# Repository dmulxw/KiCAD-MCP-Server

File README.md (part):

# Discussions. Get in here.

https://github.com/mixelpixx/KiCAD-MCP-Server/discussions/73

> ## 🚀 Meet Konnect — the next generation
>
> **[Konnect](https://github.com/mixelpixx/Konnect)** is this project rebuilt from
> scratch in Rust as a native KiCAD 10 plugin: a single binary with no runtime
> dependencies, built on KiCAD's official IPC API instead of SWIG, with 171 tools,
> bundled Claude skills and agents, design-review audits, and a manufacturing
> pipeline. It's where new development happens — licensed AGPL-3.0 (free for
> individuals and open source; commercial licenses available for businesses).
>
> This Python/TypeScript server remains fully open (MIT) and maintained.

# KiCAD MCP Server

A Model Context Protocol (MCP) server that enables AI assistants like Claude to interact with KiCAD for PCB design automation. Built on the MCP 2025-06-18 specification, this server provides comprehensive tool schemas and real-time project state access for intelligent PCB design workflows.

## Overview

The [Model Context Protocol](https://modelcontextprotocol.io/) is an open standard from Anthropic that allows AI assistants to securely connect to external tools and data sources. This implementation provides a standardized bridge between AI assistants and KiCAD, enabling natural language control of PCB design operations.

**Key Capabilities:**

- 233 tools registered, 173 of them indexed for keyword discovery
- 173 tools across 16 categories with JSON Schema validation
- Keyword tool discovery via `search_tools` / `get_category_tools`
- 23 dynamic resources exposing project state
- Complete schematic workflow with 65 tools (authoring, batch edits, hierarchy, layout) and dynamic symbol loading (~10,000 symbols)
- Freerouting autorouter integration (Java, Docker, or Podman)
- Custom footprint and symbol creation tools
- JLCPCB parts integration with 2.5M+ component catalog and local library search
- Datasheet enrichment via LCSC
- Full MCP 2025-06-18 protocol compliance
- Cross-platform support (Linux, Windows, macOS)
- Real-time KiCAD UI integration via IPC API (experimental)
- Comprehensive error handling and logging

## Try out Arduino MCP - now you can get Claude to help in the IDE, real time!:

https://github.com/mixelpixx/arduino-ide

## What's New in v2.7.0

### The bridge no longer crosses its wires

The Node-Python protocol had no request IDs: after one timeout, the next
command was silently resolved with the _previous_ command's late result, and
every response after that was off by one. Tool calls now carry an ID that
Python echoes back; stale responses are discarded instead of mis-delivered
(#373). The MCP transport also connects before Python spawns, so clients no
longer stack up against a silent server for up to two minutes during pcbnew
warm-up (#377).

### Two file-corruption classes fixed

`add_symbol_property` dropped a closing paren on every call and could splice
a unit symbol into a top-level sibling (#362, @karu2003). And S-expression
escaping is now symmetric: reads (#336) and writes (#324) share one
escape-aware implementation, so a property value containing `\"` survives a
round-trip — 419 of KiCad's own stock symbol files carry such values.

### 8 new tools

- **Validation**: `validate_schematic`, `validate_symbol_library` — locate
  structural damage with line/column, confirmed via `kicad-cli` on a copy.
- **Library tables**: `list_library_table`, `remove_library_table_entry`,
  `set_library_table_uri` — the missing CRUD around `register_*_library`.
- **Symbol editing**: `set_symbol_pin_type` (bulk pin type fixes with
  dry-run), `find_duplicate_symbols` (the same part stored twice).
- **Back-annotation**: `backannotate_footprints` — PCB footprint choices
  flow back to the schematic, the reverse of `sync_schematic_to_board`.

All by @karu2003. With #359 (@AmirF194) registering 15 existing symbol tools,
`search_tools` now indexes 169 tools in 15 categories.

### Quality of life

- `autoroute` stages its `.dsn`/`.ses` work files in a temp directory and
  cleans up on every exit — no more litter next to your board, no stale-SES
  imports, and a killed run says "terminated externally" instead of
  `exit code 4294967295` (#249, scoped by @Dewieinns' traces).
- Placed symbols inherit the library's default Footprint (#300,
  implementation by @stefangordon).
- `add_layer` actually adds inner copper layers (#222) — it previously wrote
  to non-copper layer IDs and renamed F.SilkS.
- `sync_schematic_to_board` matches by symbol UUID, not just refdes (#250).
- JLCPCB tools decode the new upstream `source-db-v2` schema (#352,
  @stefanobaldo) and degrade gracefully when the parts DB is unavailable
  (#264, @fage2022).
- `setup-macos.sh --verify` now fails when Python requirements are missing
  instead of passing on a server that cannot start (#350, @francisrath).

Full details in the [CHANGELOG](CHANGELOG.md).

## What's New in v2.6.0

### A session-killing bug is fixed

Deleting anything from a board — a component, a trace, a board outline —
worked exactly once. The next operation, even a pure read, failed with a
`SwigPyObject` error, and only `close_project` then `open_project` recovered.
`BOARD.Remove()` hands C++ ownership to Python, so dropping the reference ran
a destructor on an object KiCad still pointed at, corrupting SWIG state
process-wide. Six call sites were affected; all now use `BOARD.Delete()`.

### 10 new tools

- **Vendor PCB import**: `import_pcb` converts PADS, Altium, Eagle, CADSTAR,
  Fabmaster, P-CAD, SolidWorks PCB and binary Cadence Allegro `.brd` files via
  KiCad 10's native importer.
- **Hierarchical schematics**: `remove_hierarchical_sheet`,
  `set_sheet_property`, `get_sheet_properties`, and `hierarchical_place` for
  arranging footprints by schematic hierarchy.
- **Schematic lint and repair**: `lint_offgrid` finds and safely snaps
  off-grid geometry that silently breaks junction placement;
  `repair_flat_symbols` fixes SnapEDA/SamacSys symbols that crash kicad-skip;
  `lint_schematic_cosmetic` tidies pin names and label orientation.
- **Board origins**: `set_board_origin` / `get_board_origin`.

### Your `.kicad_pro` net classes stop disappearing

Board saves no longer let pcbnew serialize a stale in-memory project model
over your hand-edited net classes and `netclass_patterns`. Opening a project
no longer rewrites the file at all.

### Breaking: schematic tools fail loudly on an unparseable sheet

Tools that used to return partial or empty results now return a structured
`schematic_load_failed` error naming the offending symbols. Silently skipping
a broken sheet produced an incomplete pad-to-net map reported as success,
which is worse. `repair_flat_symbols` fixes the usual cause. See
[KNOWN_ISSUES.md](docs/KNOWN_ISSUES.md) section 7.

Full details in the [CHANGELOG](CHANGELOG.md).

## What's New in v2.5.0

### 20 new board-lifecycle and geometry tools

- **Lifecycle**: `open_board`, `reload_board`, `save_board`, `save_as`,
  `is_dirty`, `discard_or_reload`, `create_board_from_schematic`.
- **Graphics editing**: `clear_board_outline`, `replace_board_outline`,
  `list_graphics`, `delete_graphic`, `update_graphic`, `move_footprint_text`.
- **Geometry queries**: `batch_move_components`, `get_component_geometry`,
  `get_pads`, `get_net_pads`, `get_ratsnest`, `estimate_airwire_lengths`,
  `check_placement_clearance`.

All of them respect backend session pinning, so a board saved while KiCad's
GUI owns the session routes to the GUI rather than writing a stale in-memory
copy — including the awkward case where `save_as` changes the board's
identity mid-session.

### Formatting is normalized and enforced

- `pre-commit run --all-files` (black, isort, prettier, flake8, mypy, eslint)
  is now a real CI gate, which is what CONTRIBUTING has always claimed.
- `npm run lint` used to run `black` in **write** mode against whatever
  `black` was on `PATH`, silently reformatting your working tree with a
  version that disagreed with CI. It now checks only; `npm run format:py` is
  the write path.
- The README's tool count is pinned to the registry by a test, so it
  self-corrects instead of drifting.

Full details in the [CHANGELOG](CHANGELOG.md).

## What's New in v2.4.1

### Three tools that were registered but had no backend now work

- `assign_net_to_class`, `check_clearance` and `set_layer_constraints` each had
  a full schema and a router entry but no dispatch handler, so every call
  returned `Unknown command`. Found by a documentation-coverage audit.
- Per-layer constraints are written to a project-scoped `.kicad_dru`
  custom-rules file, which `kicad-cli pcb drc` and the GUI both pick up — there
  is no pcbnew API for them.

### Silent failures removed

- `autoroute` was abandoned by the Node bridge at 30 s while Freerouting was
  still running, reporting failure against a valid `.ses` that existed on disk.
  Its timeout now derives from the `timeout` and `attempts` you pass.
- `get_board_2d_view` omitted `--layers` entirely when no layers were given,
  and KiCad 9+ then refuses the export — producing no file at all.
- `create_zone` raised `AttributeError` on every call over the IPC backend.

### New part-sourcing tools

- `search_parts_registry` / `get_registry_part` / `download_registry_part`
  reuse a verified existing footprint or symbol instead of generating one.
  Downloads are host-allowlisted, extension-checked and size-capped.
- `get_jlcpcb_part` returns live stock and tiered pricing when JLCPCB Open
  Platform credentials are configured, falling back to the local snapshot.

### CI now actually runs the test suite

- The Python job had been a no-op in four independent ways, and Actions was
  disabled repo-wide — 32 failed runs and 0 successes across the project's
  whole history. All 1551 Python and 63 TypeScript tests now gate every push.

Full details in the [CHANGELOG](CHANGELOG.md).

## What's New in v2.4.0

### Symbol library management

- `import_symbol` / `export_symbol` / `rename_symbol` copy a symbol between
  `.kicad_sym` libraries, extract one to a standalone file, and rename a
  symbol including its sub-symbol shards and any `(extends ...)` references
  from derived symbols in the same library.
- `add_symbol_property` and `add_library_symbol_property` set custom BOM
  fields (Manufacturer, MPN, LCSC, ...) on a library symbol or on a
  schematic's cached definition.
- `update_symbol_from_library` refreshes cached `lib_symbols` definitions
  across one schematic, a list, or every project under a directory —
  the programmatic equivalent of KiCad's Update Symbol from Library.
- `replace_instance_lib_ids` swaps `lib_id` references per an explicit
  old-to-new mapping, for migrating a schematic between libraries.

### Faster symbol discovery

- Library directories, resolved paths, extracted symbol blocks, and parsed
  symbol lists are now cached process-wide instead of being rebuilt for every
  component add. Staleness guards revalidate paths and track source `mtime_ns`,
  and the mutating write paths clear the caches explicitly.

### Fixes that restore basic operation

- Every `.kicad_sym` and schematic write raised `TypeError` on Python 3.9, the
  project's declared floor — `Path.write_text` did not accept `newline` until
  3.10.
- JLCPCB part search could not find hyphenated MPNs.
- Eagle import wrote a KiCad 9 schematic header; it now writes the KiCad 10
  header, verified against real `kicad-cli` 10.0.
- Component placement snaps to the 1.27 mm grid, `import_ses` no longer
  creates phantom slashless nets, and `export_dsn`/`autoroute` keep
  `.kicad_pro` net classes.

Full details in the [CHANGELOG](CHANGELOG.md).

## What's New in v2.3.1

### Eagle schematic import

- `import_eagle_schematic` converts Eagle `.sch` XML designs to KiCad format
  with symbol mapping, net wires, multi-gate parts, dangling-wire pruning,
  and ground-truth ERC reporting via `kicad-cli`.

### 3D model tools and interactive reload

- `add_component_3d_model` / `remove_component_3d_model` for attaching
  STEP/WRL models to footprints.
- Opt-in `KICAD_INTERACTIVE_SCHEMATIC=1` auto-confirms KiCad's reload dialog
  on Windows after schematic writes.

### Scaffolding cluster complete

- New projects start blank (no `_TEMPLATE_*` symbols leaked into user files).
- `.kicad_pro` files match what KiCad itself writes.
- Format version `20260101` ensures all KiCad 10.0.x builds can open
  generated schematics.

### KiCad 10 compatibility

- Derived symbols in `.kicad_symdir` libraries resolve their parent from
  sibling shards.
- Unified install discovery finds relocated Windows installs via registry.
- User env-var placeholders from `kicad_common.json` are resolved in library
  paths.
- Phantom cross-unit pin reports in `get_wire_connections` are eliminated.

Full details in the [CHANGELOG](CHANGELOG.md).

## What's New in v2.3.0

### Schematic corruption on KiCad 10 — both mechanisms fixed

- **Complete instance blocks**: placed components now carry the real project
  name, root-sheet uuid path, per-pin uuid entries (ERC can bind wires to
  pins), and the full KiCad 10 field set — verified byte-equivalent to what
  eeschema itself writes. Previously, dragging or editing a placed symbol
  could crash KiCad.
- **Canonical multi-line writes**: schematic tools no longer minify the whole
  file onto one line. Tool writes now match eeschema's "Save" byte-for-byte,
  with a self-check on every write that can never corrupt data. Already-
  minified files are repairable with `scripts/kicad_sch_reformat.py`.

### Your edits are protected

- **Backend session pinning**: a loaded project stays on one backend
  (SWIG or IPC) for its whole lifecycle — saves can no longer silently route
  to a stale GUI board and lose your edits.
- **External-edit guard**: `save_project` refuses to overwrite a board file
  whose contents changed on disk since load (pass `force: true` to override).
- **`close_project`** (new tool): release the project so files can be edited
  directly, then reopen — no more restart choreography.

### Works on a stock Windows install

- `kicad-cli` and 7-Zip are resolved from their install locations even when
  not on PATH — un-breaking exports, ERC/DRC, netlists, board views, and the
  JLCPCB database download, each with actionable errors when truly missing.

### New layout tools

- `suggest_placement`: connectivity-driven PCB placement optimizer (dry-run
  by default, deterministic).
- `suggest_schematic_declutter`: re-orients overlapping net labels without
  touching connectivity.

Plus KiCad 10 compatibility fixes (sheet renames, sharded `.kicad_symdir`
libraries, IPC `Box2` board size), correct pin geometry for rotated+mirrored
and multi-unit symbols, bounded IPC connects with SWIG fallback, and a real
Vitest suite for the TypeScript layer. Full details in the
[CHANGELOG](CHANGELOG.md).

## What's New in v2.2.3

### New Tools: FFC/Ribbon Cable Passthrough Workflow

A complete workflow for designing passthrough adapter boards (e.g. Raspberry Pi CSI
cable adapters) is now supported:

1. `connect_passthrough` — wires all pins of one connector to the matching pins of
   another in the schematic (J1 pin N → J2 pin N, auto-named nets).
2. `sync_schematic_to_board` — imports the net assignments into the PCB.
3. `route_pad_to_pad` — routes each connection with automatic via insertion when
   pads are on opposite copper layers.
4. `snapshot_project` — saves a named checkpoint into `<project>/snapshots/`.

### Bug Fixes (KiCAD 9 / Windows)

- **Via insertion for B.Cu footprints** — `route_pad_to_pad` now correctly detects
  when a footprint is on B.Cu and inserts the required via. (KiCAD 9 SWIG returned
  `F.Cu` for all SMD pads regardless of layer — fixed.)
- **Board outline rounded corners** — `add_board_outline` now correctly applies
  `cornerRadius` when `shape="rounded_rectangle"`.
- **B.Cu placement hang** — placing a footprint on B.Cu no longer causes a ~30s
  freeze in KiCAD 9.

### Developer Mode

Set `KICAD_MCP_DEV=1` in your Claude Desktop MCP environment to automatically save
the MCP session log into the project's `logs/` folder on every `export_gerber` and
`snapshot_project` call. Useful for debugging and for attaching to GitHub issues.

```json
"env": {
  "KICAD_MCP_DEV": "1"
}
```

> **Privacy warning:** The session log contains your full tool call history
> (including file paths and design details). **Review or delete `logs/` before
> sharing a project directory publicly.**

See [CHANGELOG](CHANGELOG.md) for the full list of changes in this release.

---

## What's New in v2.1.0

### Critical Schematic Workflow Fix + Complete Wiring System (Issue #26)

The schematic workflow was completely broken in previous versions - **this is now fixed AND dramatically enhanced!**

**What was broken:**

- `create_project` only created PCB files, no schematics
- `add_schematic_component` called non-existent API methods
- Schematics couldn't be created or edited at all
- Only 13 component types available (severe limitation)
- No working wire/connection functionality

**Complete Implementation (3 Phases):**

**Phase 1: Component Placement Foundation**

- `create_project` now creates both .kicad_pcb and .kicad_sch files
- Added pre-configured template schematics with 13 common component types
- Rewrote component placement to use proper `clone()` API

**Phase 2: Dynamic Symbol Loading (BREAKTHROUGH!)**

- **Access to ALL ~10,000 KiCad symbols** from standard libraries
- Automatic detection and dynamic loading from `.kicad_sym` library files
- Zero configuration required - just specify library and symbol name
- Seamless integration with existing MCP tools
- Full S-expression parsing and injection system

**Phase 3: Intelligent Wiring System (NEW in v2.1.0)**

- **Automatic pin location discovery** with rotation support (0°, 90°, 180°, 270°)
- **Smart wire routing** (direct, orthogonal horizontal-first, orthogonal vertical-first)
- **Power symbol support** (VCC, GND, +3V3, +5V, etc.)
- **Wire graph analysis** - geometric tracing for net connectivity
- **Net label management** (local, global, hierarchical labels)
- **Netlist generation** with accurate component/pin connections

**Technical Architecture:**
The kicad-skip library cannot create symbols or wires from scratch. We implemented a comprehensive solution:

1. **Static Templates:** 13 pre-configured symbols (R, C, L, LED, etc.) for instant use
2. **Dynamic Loading:** On-demand injection of ANY symbol from KiCad libraries:
   - Parse `.kicad_sym` library files using S-expression parser
   - Inject symbol definition into schematic's `lib_symbols` section
   - Create offscreen template instance
   - Reload schematic so kicad-skip sees new template
   - Clone template to create actual component
3. **Wire Creation:** S-expression-based wire injection (bypasses kicad-skip API limitations)
4. **Pin Discovery:** Parse symbol definitions, apply rotation transformations, calculate absolute positions
5. **Connectivity Analysis:** Geometric wire tracing to build net connection graphs

**Example - Complete Circuit Creation:**

```python
# Load power symbols dynamically
loader.load_symbol_dynamically(sch_path, "power", "VCC")

# Place components with auto-rotation
ComponentManager.add_component(sch, {
    "type": "STM32F103C8Tx",
    "library": "MCU_ST_STM32F1",
    "reference": "U1",
    "x": 100, "y": 100, "rotation": 0
})

# Connect with intelligent routing
ConnectionManager.add_connection(sch_path, "U1", "1", "R1", "2", routing="orthogonal_h")

# Connect to power nets
ConnectionManager.connect_to_net(sch_path, "U1", "VDD", "VCC")

# Analyze connectivity
connections = ConnectionManager.get_net_connections(sch, "VCC", sch_path)
# Returns: [{"component": "U1", "pin": "VDD"}, {"component": "R1", "pin": "1"}]
```

**Test Results:**

- Component placement: 100% passing
- Dynamic symbol loading: 10,000+ symbols accessible
- Wire creation: 100% passing (8/8 connections in test circuit)
- Pin discovery: Rotation-aware, sub-millimeter accuracy
- Net connectivity: 100% accurate (VCC: 2 connections, GND: 4 connections)
- Netlist generation: Working with accurate pin-level connections

See [Schematic Tools Reference](docs/SCHEMATIC_TOOLS_REFERENCE.md) for the complete schematic tool documentation, and the [Headless Authoring Guide](docs/HEADLESS_AUTHORING.md) for field-tested practice driving these tools without the KiCad GUI.

### IPC Backend (Experimental)

We are currently implementing and testing the KiCAD 9.0 IPC API for real-time UI synchronization:

- Changes made via MCP tools appear immediately in the KiCAD UI
- No manual reload required when IPC is active
- Hybrid backend: uses IPC when available, falls back to SWIG API
- IPC runtime reconnect: if MCP has fallen back to SWIG, IPC-capable board
  tools retry IPC after KiCAD launches instead of staying on SWIG for the entire
  session
- 20+ commands now support IPC including routing, component placement, and zone operations

Note: IPC features are under active development and testing. Enable IPC in KiCAD via Preferences > Plugins > Enable IPC API Server.

For OpenCode on Windows, the backend can be configured as `auto`, `ipc`, or
`swig` during setup. See [OpenCode (Windows)](#opencode-windows) for the
configuration command and backend options.

### Tool Discovery

Every tool is registered individually, so an MCP client can call any of them by
name. On top of that, most tools are indexed so an assistant can find one by
keyword instead of guessing:

- **32 essential tools** that `search_tools` surfaces first, covering the
  operations nearly every session needs
- **173 tools indexed across 16 categories** (board, component, export, drc,
  schematic, library, symbol_library, symbol_pins, schematic_hierarchy,
  schematic_layout, schematic_batch, routing, autoroute, validation,
  parts-registry, digikey)
- **3 discovery tools**:
  - `list_tool_categories` - Browse all available categories
  - `get_category_tools` - View tools in a specific category
  - `search_tools` - Find tools by keyword

The remaining 60 registered tools are not indexed yet. They work exactly the
same when called by name; they simply do not appear in `search_tools` results.

**Why this matters:** the assistant can locate the right tool for your task by
keyword rather than inventing a name. Note that discovery does _not_ reduce
context: every tool schema is still sent to the client. An earlier design hid
tools behind an `execute_tool` dispatcher to save context; it was removed
because the model then invented schemas it had never been shown. See
[ROUTER_ARCHITECTURE.md](docs/ROUTER_ARCHITECTURE.md) for that history.

**Usage is seamless:** Just ask naturally - "export gerber files" or "add mounting holes" - and Claude will find and call the appropriate tools automatically.

### NEEDS TESTING - REPORT ISSUES

### JLCPCB Parts Integration (New!)

Complete integration with JLCPCB's parts catalog, providing two complementary approaches for component selection:

**Dual-Mode Architecture:**

1. **Local Symbol Libraries** - Search JLCPCB libraries installed via KiCAD Plugin and Content Manager (contributed by [@l3wi](https://github.com/l3wi))
2. **JLCPCB API Integration** - Access the complete 2.5M+ parts catalog with real-time pricing and stock data

**Key Features:**

- Real-time pricing with quantity breaks (1+, 10+, 100+, 1000+)
- Stock availability checking
- Basic vs Extended library type identification (Basic = free assembly)
- Intelligent cost optimization with alternative part suggestions
- Package-to-footprint mapping for KiCAD compatibility
- Parametric search by category, package, manufacturer
- Local SQLite database for fast offline searching
- No API credentials required for local library search

**Why this matters:** JLCPCB offers PCB assembly services where Basic parts have no assembly fee, while Extended parts charge $3 per unique component. This integration helps you find the cheapest components with the best availability, potentially saving hundreds of dollars on assembly costs for production runs.

See [JLCPCB Usage Guide](docs/JLCPCB_USAGE_GUIDE.md) for detailed setup and usage instructions.

### Comprehensive Tool Schemas

Every tool now includes complete JSON Schema definitions with:

- Detailed parameter descriptions and constraints
- Input validation with type checking
- Required vs. optional parameter specifications
- Enumerated values for categorical inputs
- Clear documentation of what each tool does

### Resources Capability

Access project state without executing tools:

- `kicad://project/current/info` - Project metadata
- `kicad://project/current/board` - Board properties
- `kicad://project/current/components` - Component list (JSON)
- `kicad://project/current/nets` - Electrical nets
- `kicad://project/current/layers` - Layer stack configuration
- `kicad://project/current/design-rules` - Current DRC settings
- `kicad://project/current/drc-report` - Design rule violations
- `kicad://board/preview.png` - Board visualization (PNG)

### Protocol Compliance

- Updated to MCP SDK 1.21.0 (latest)
- Full JSON-RPC 2.0 support
- Proper capability negotiation
- Standards-compliant error codes

## Available Tools

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
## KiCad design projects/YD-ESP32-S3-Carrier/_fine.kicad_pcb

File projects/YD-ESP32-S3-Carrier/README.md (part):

# LANFENG-ESP32-S3 载板 (Carrier Board)

把 **YD-ESP32-S3 开发板 + ES8311 语音模块 + 1.77" SPI TFT + 3.7V 锂电池** 从一堆杜邦线变成一块插起来就能用的积木。

- 板子尺寸 **100 × 64 mm**，2 层，板厚 1.6 mm
- 四角 **4 × Ø3.2 mm 非金属化螺丝孔**（NPTH，无铜），孔心内缩 4.5 mm
- 板高 64 mm 是**按开发板 USB 边缘定的**：开发板本体到 y 63.25 为止，Type-C 口整个悬在板外，装壳不挡
- 连接器：**排母为主 + 排针引出**
  - 开发板 2 × 1×22 排母（J1/J2）
  - 语音模块 1×10 排母（J3）
  - 显示屏 1×7 排针（J4）、电池 1×2 排针（J5）
  - 备用 IO 1×8 ×2（J6/J7）、串口 1×3（J9）
- 语音模块**平放**在板上（J3 上方整块区域无元件、无过孔）
- 四个按键**同在一条底边**：音量+、音量−、激活、Reset
- **板载 3.7V 锂电充电 + 升压**，USB 与电池可同时插，自动由 USB 供电

---

## 一、接线表

### 1. 开发板插到 J1 / J2（**照丝印插，别照原理图**）

两列排母间距 **25.40 mm**，脚距 2.54 mm，每列**最上方都是第 1 脚**。

> ⚠️ **重要**：开发板原理图 `J2` 的引脚编号与实物丝印**差一位**（原理图 pin1 = TXD0，实物最上方是 GND）。本载板**以实物丝印为准**，丝印上每一脚都印了 GPIO 号，插之前对一下即可。

**J1（左列，上→下）**

| 脚 | 丝印 | 脚 | 丝印 | 脚 | 丝印 |
|---|---|---|---|---|---|
| 1 | 3V3 | 9 | IO16 | 17 | IO11 |
| 2 | 3V3 | 10 | IO17 | 18 | IO12 |
| 3 | RST | 11 | IO18 | 19 | IO13 |
| 4 | IO4 | 12 | IO8 | 20 | IO14 |
| 5 | IO5 | 13 | IO3 | 21 | **5V** |
| 6 | IO6 | 14 | IO46 | 22 | GND |
| 7 | IO7 | 15 | IO9 | | |
| 8 | IO15 | 16 | IO10 | | |

**J2（右列，上→下）**

| 脚 | 丝印 | 脚 | 丝印 | 脚 | 丝印 |
|---|---|---|---|---|---|
| 1 | GND | 9 | IO39 | 17 | IO47 |
| 2 | IO43 | 10 | IO38 | 18 | IO21 |
| 3 | IO44 | 11 | IO37 | 19 | IO20 |
| 4 | IO1 | 12 | IO36 | 20 | IO19 |
| 5 | IO2 | 13 | IO35 | 21 | GND |
| 6 | IO42 | 14 | IO0 | 22 | GND |
| 7 | IO41 | 15 | IO45 | | |
| 8 | IO40 | 16 | IO48 | | |

> **J1-21 是整块板的 5V 入口**：开发板的 Type-C 收进来的 5V 从这里回灌到载板的 `+5V` 轨，
> 给功放、指示灯和充电电路供电。所以**充电宝要插在开发板的 Type-C 口**，不是载板。

### 2. 语音模块插到 J3（1×10 排母，模块**平放**）

丝印按**模块自己的引脚名**印，照着插就行：

| J3 | 1 | 2 | 3 | 4 | 5 | 6 | 7 | 8 | 9 | 10 |
|---|---|---|---|---|---|---|---|---|---|---|
| 丝印 | SDA | SCL | MCK | BCK | DI | WS | DO | 3V3 | VCC | GND |
| 接到 | GPIO1 | GPIO2 | GPIO3 | GPIO15 | GPIO7 | GPIO16 | GPIO6 | 3V3 | **5V** | GND |

> 注意 **VCC 接 5V**（模块功放取 5V），**3V3 接 3V3**，两个别接反。

### 3. 显示屏用排线引到 J4（1×7 排针）

| J4 | 1 | 2 | 3 | 4 | 5 | 6 | 7 |
|---|---|---|---|---|---|---|---|
| 丝印 | CS | DC | RST | SDA | SCK | VCC | GND |
| 接到 | GPIO41 | GPIO40 | GPIO45 | GPIO47 | GPIO21 | 3V3 | GND |

### 4. 电池接到 J5（1×2 排针，2.54 mm）

| J5 | 1 | 2 |
|---|---|---|
| 丝印 | **BAT** | GND |

接 **3.7V 聚合物锂电池**（2.54 mm 插头，红=BAT、黑=GND）。
**BAT 这一脚是电池的裸正极**，在 SW5 之前——关掉 SW5 就彻底断开电池放电，但**充电不受影响**（TP4056 直接挂在电池上）。

> v1 这一脚印的是 `+5V`，因为电池当时是直接并在 5V 轨上的。v2 中间加了升压，所以标签必须改。

### 5. 备用 IO（J6 / J7）与串口（J9）

每个 GPIO **只引一次**，两个排针没有重复脚位。

**J6 —— J1 侧空余脚**

| 脚 | 1 | 2 | 3 | 4 | 5 | 6 | 7 | 8 |
|---|---|---|---|---|---|---|---|---|
| 丝印 | 3V3 | GND | IO9 | IO10 | IO11 | IO12 | IO13 | IO14 |

**J7 —— J2 侧空余脚**

| 脚 | 1 | 2 | 3 | 4 | 5 | 6 | 7 | 8 |
|---|---|---|---|---|---|---|---|---|
| 丝印 | 3V3 | GND | IO42 | IO39 | IO38 | IO48 | IO43 | IO44 |

**J9 —— UART1**（右下角，按键上方）

| 脚 | 1 | 2 | 3 |
|---|---|---|---|
| 丝印 | IO17 | IO18 | GND |

IO17/IO18 正是 ESP32-S3 **UART1** 的 TX/RX，单独引一组当调试串口。

> **刻意不引出**：IO0 / IO46（strapping 脚）、IO19 / IO20（USB D±）、IO35 / 36 / 37（PSRAM 占用）。
> 这 7 个脚在 J1/J2 上保留焊盘但**不接任何网络**，也不引到 J6/J7。

### 6. 按键（都在底边一排）

| 按键 | 丝印 | 接到 |
|---|---|---|
| SW1 | VOL+ | GPIO4 |
| SW2 | VOL− | GPIO5 |
| SW3 | ACT | GPIO8 |
| SW4 | RESET | CHIP_PU（开发板 RST） |
| SW5 | PWR SW | 电池 → 升压（电源开关，不是按键） |

四个按键另一端全接 GND，靠 ESP32-S3 **内部上拉**，不需要外部电阻。
GPIO4 / GPIO5 / GPIO8 都避开了 strapping 脚和 USB 脚。

---

## 二、元件清单

共 **36 个封装**。

### 连接器 / 机电件

| 位号 | 值 | 封装 |
|---|---|---|
| J1, J2 | YD-ESP32-S3_L / _R | `PinSocket_1x22_P2.54mm_Vertical` |
| J3 | ES8311_AUDIO | `PinSocket_1x10_P2.54mm_Vertical` |
| J4 | TFT_1.77 | `PinHeader_1x07_P2.54mm_Vertical` |
| J5 | BAT_3V7 | `PinHeader_1x02_P2.54mm_Vertical` |
| J6, J7 | SPARE_IO_A / _B | `PinHeader_1x08_P2.54mm_Vertical` |
| J9 | UART1 | `PinHeader_1x03_P2.54mm_Vertical` |
| SW1–SW4 | VOL_UP / VOL_DN / ACTIVATE / RESET | `SW_PUSH_6mm` |
| SW5 | POWER_ON_OFF | `SW_Slide_SPDT_Straight_CK_OS102011MS2Q` |
| H1–H4 | MountingHole_3.2mm_M3 | Ø3.2 mm NPTH |

### 直插（滤波 / 指示）

| 位号 | 值 | 封装 |
|---|---|---|
| C1 | 100 µF 电解（5V 储能） | `CP_Radial_D5.0mm_P2.50mm` |
| C2 | 100 nF 瓷片（5V 去耦） | `C_Disc_D5.0mm_W2.5mm_P5.00mm` |
| C3 | 10 µF 电解（3V3） | `CP_Radial_D5.0mm_P2.50mm` |
| C4 | 100 nF（3V3 去耦） | `C_Disc_D5.0mm_W2.5mm_P5.00mm` |
| D1 | PWR_LED（电源指示） | `LED_D5.0mm` |
| R1 | 1 kΩ（D1 限流） | `R_Axial_DIN0207_L6.3mm_D2.5mm_P7.62mm_Horizontal` |

### 贴片（充电 + 升压）

| 位号 | 值 | 封装 | 作用 |
|---|---|---|---|
| U1 | TP4056 | `Package_SO:SOIC-8-1EP_3.9x4.9mm_P1.27mm_EP2.41x3.3mm_ThermalVias` | 锂电池充电 |
| U2 | MT3608 | `Package_TO_SOT_SMD:SOT-23-6` | 3.7V→4.89V 升压 |
| D2 | SS34 | `Diode_SMD:D_SMA` | 升压输出 OR 二极管 |
| D3 | CHG（充电指示） | `LED_SMD:LED_0805_2012Metric` | 充电中点亮 |
| L1 | 22 µH 屏蔽电感 | `Inductor_SMD:L_Taiyo-Yuden_NR-60xx` | 升压储能 |
| R2 | 2.4 kΩ | `Resistor_SMD:R_0805_2012Metric` | 充电电流 ≈ 500 mA |
| R3 | 1 kΩ | `Resistor_SMD:R_0805_2012Metric` | D3 限流 |
| R4 | 71.5 kΩ | `Resistor_SMD:R_0805_2012Metric` | FB 上分压 |
| R5 | 10 kΩ | `Resistor_SMD:R_0805_2012Metric` | FB 下分压 |
| C5, C6 | 10 µF | `Capacitor_SMD:C_1206_3216Metric` | TP4056 输入 / 电池侧 |
| C7, C8 | 22 µF | `Capacitor_SMD:C_1206_3216Metric` | 升压输入 / 输出 |

---

## 三、打样说明（嘉立创）

**直接上传 `gerbers/` 整个目录**即可，EDA 软件会自动识别。

| 项目 | 取值 |
|---|---|
| 尺寸 | **100 × 64 mm**（在 100×100 以内，标准价） |
| 层数 | 2 层 |
| 板厚 | 1.6 mm |
| 阻焊 / 丝印 | 默认即可 |
| 表面处理 | 有铅喷锡 / 无铅喷锡均可 |
| 最小线宽 / 间距 | 0.30 mm / 0.16 mm |
| 最小孔径 | **0.30 mm**（过孔）／**3.20 mm**（螺丝孔） |
| 过孔 | Ø0.60 / 钻孔 Ø0.30 |
| 丝印 | 最小字符高 0.80 mm、线宽 0.15 mm（满足嘉立创工艺下限） |

> **本板有 13 个贴片元件**，不是纯插件板——需要贴片焊接（见第四节）。
> 钢网层（`F_Paste` / `B_Paste`）**必须一起上传**，否则贴片无法生产。

Gerber 文件说明（Protel 扩展名，嘉立创可直接识别）：

```
gerbers/
  YD-ESP32-S3-Carrier-F_Cu.gtl          顶层铜
  YD-ESP32-S3-Carrier-B_Cu.gbl          底层铜
  YD-ESP32-S3-Carrier-F_Silkscreen.gto  顶层丝印
  YD-ESP32-S3-Carrier-B_Silkscreen.gbo  底层丝印
  YD-ESP32-S3-Carrier-F_Mask.gts        顶层阻焊
  YD-ESP32-S3-Carrier-B_Mask.gbs        底层阻焊
  YD-ESP32-S3-Carrier-F_Paste.gtp       顶层钢网（贴片用，务必上传）
  YD-ESP32-S3-Carrier-B_Paste.gbp       底层钢网
  YD-ESP32-S3-Carrier-Edge_Cuts.gm1     板框
  YD-ESP32-S3-Carrier-PTH.drl           金属化孔（插件脚 + 过孔）
  YD-ESP32-S3-Carrier-NPTH.drl          非金属化孔（4 个 Ø3.2 螺丝孔）
  YD-ESP32-S3-Carrier-*-drl_map.gbr     钻孔图（仅参考）
  YD-ESP32-S3-Carrier-job.gbrjob        Gerber 作业文件
```

---

## 四、装配注意事项

1. **先贴片，后直插**：
   `U1 U2 D2 D3 L1 R2 R3 R4 R5 C5 C6 C7 C8`（回流焊或热风）→ 按键 SW1–SW4 → 电容 C1–C4、D1、R1 → 排针 J4/J5/J6/J7/J9 → 排母 J1/J2/J3 → 最后 SW5。
2. **U1（TP4056）是 ESOP-8 带散热焊盘**，散热脚下的 9 个过孔是散热路径，纯烙铁很难焊透。**用热风枪或加热台**；只有烙铁的话，建议改买 **SOP-8 无散热焊盘版**的 TP4056 并手工替换封装。
3. **排母焊在正面**（F.Cu 那面），开发板和语音模块从正面插下去。
4. **语音模块方向**：模块主体朝板内平铺，1 脚对准 J3 丝印的 `SDA`。J3 上方整块区域（x 43–74, y 15–32）刻意留空，模块能完全放平。
5. **D1 / D3 极性**：LED 封装 1 脚是阴极（有横杠/缺口的一侧）。D1 阴极接 GND，D3 阴极接 U1 的 `CHRG`。
6. **D2（SS34）方向**：1 脚是阴极，接 `+5V` 轨；2 脚是阳极，接升压输出。**装反 = 电池供不了电**。
7. **C1 / C3 是电解电容，注意极性**：丝印上有 `+` 号的那一脚接正。
8. **螺丝孔是 Ø3.2 mm 非金属化通孔**，孔周围 2.70 mm 内没有覆铜——如果螺丝头/垫片需要落在铜面上，请在此处垫绝缘片。

---

## 五、电源设计（v2 的核心改动）

### 5.1 为什么必须升压

v1 把电池直接并在 `+5V` 轨上。那是错的，而且没法靠加二极管救：
**3.7V − 0.45V = 3.25V**，开发板的 AMS1117 压差要 1.1V，3.25V 根本推不动 3.3V 轨。

所以 v2 在电池和 5V 轨之间加了 **MT3608 升压**，并在 5V 轨上加了 **TP4056 充电**：

```
充电宝 5V ──Type-C──> 开发板 5V ──J1-21──┬──> +5V 轨 ──> J3-9(功放VCC) / C1,C2 / R1,D1 / C8 / R3,D3
                                          │
                                 D2(SS34) ┘   ← 阴极朝 +5V，阳极朝升压输出
                                     ▲
  LiPo 3.7V ──J5─┬─> U1 TP4056 (BAT) ──> 充电，直接挂在电池上
                 │
                 └─> SW5 ─> U2 MT3608 ──> D2 阳极
                              └─ FB 分压从 +5V（D2 之后）取
```

### 5.2 为什么 FB 分压取在二极管**之后**，输出定到 **4.89 V**

这是让"USB 优先"**自动**成立的关键，两个细节缺一不可：

1. **FB 取在 D2 之后（即取 `+5V`）** —— 二极管压降被反馈环包进去了，输出电压与负载电流无关。
   如果 FB 取在 D2 之前，带载时二极管压降会让 `+5V` 掉到 4.5V 以下。
2. **输出定在 4.89 V < USB 的 5.0 V** —— USB 一插上，D2 阴极 (5.0V) 高于阳极 (4.89V)，
   **二极管自然反偏截止**，升压 IC 因输出被顶高而停止开关，进入待机。
   不需要任何"检测电路"，也不需要手动切换。

分压电阻：`Vout = 0.6 × (1 + R4/R5)` → **R4 = 71.5 kΩ / R5 = 10 kΩ → 4.89 V**。

电池单独供电时 `+5V` = 4.89V，对 AMS1117（需 ≥4.4V）和功放（功率 ∝ V²，仅降 4%）都完全够用。

### 5.3 几个容易被忽略的点

- **SW5 放在电池与升压之间**，不是放在 5V 轨上。关掉即彻底切断电池放电；充电不受影响。
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
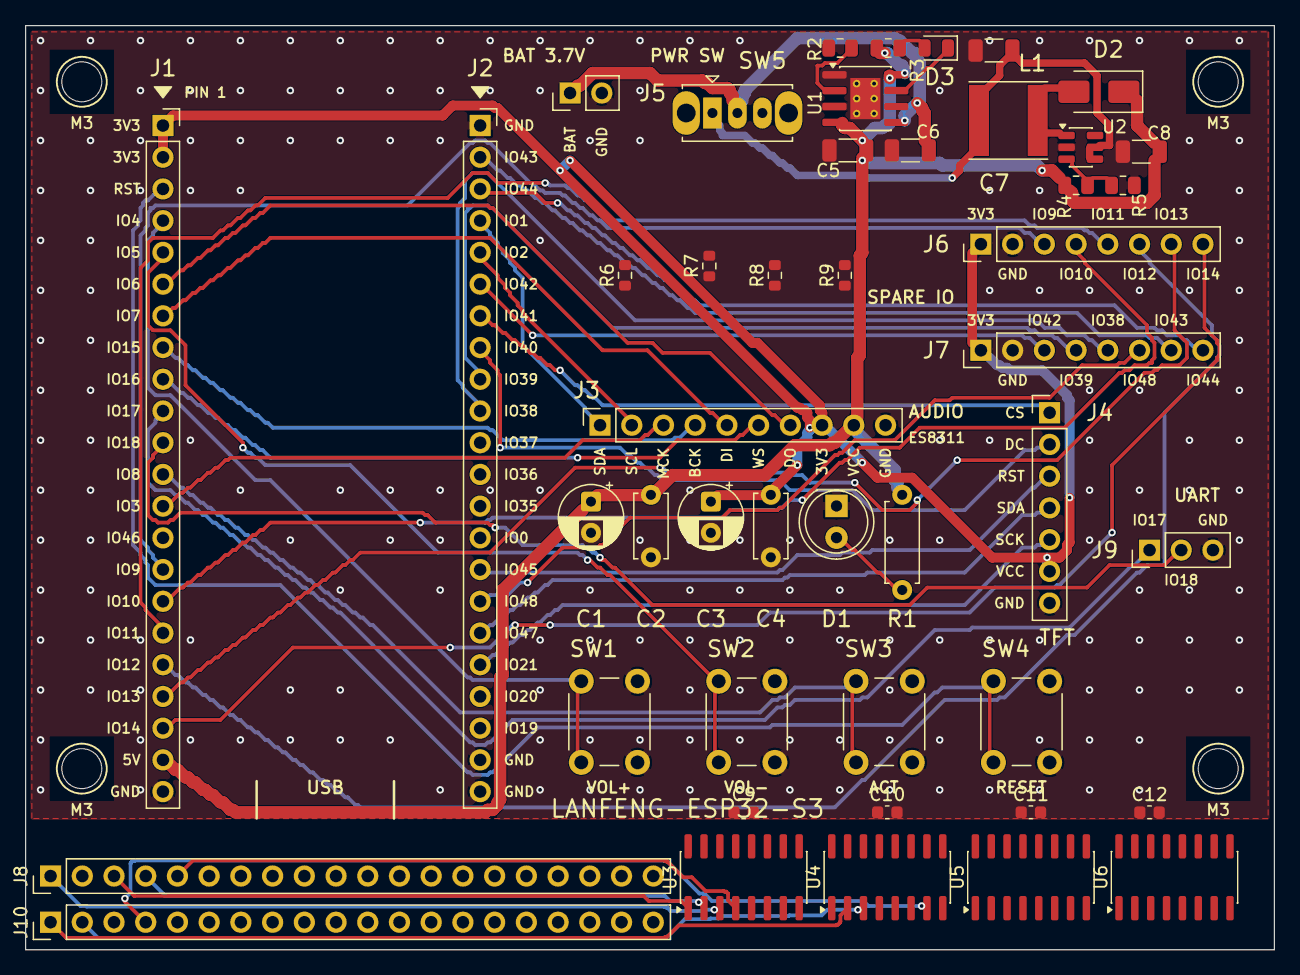
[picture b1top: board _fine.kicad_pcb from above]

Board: 2 copper layers, 100.0 x 74.0 mm, 50 parts (0 on the bottom side), 75 nets.

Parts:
C1: 100uF; CP_Radial_D5.0mm_P2.50mm
C2, C4: 100nF; C_Disc_D5.0mm_W2.5mm_P5.00mm
C3: 10uF; CP_Radial_D5.0mm_P2.50mm
C5, C6: 10uF; C_1206_3216Metric
C7, C8: 22uF; C_1206_3216Metric
C9, C10, C11, C12: 100nF; C_0603_1608Metric
D1: PWR_LED; LED_D5.0mm
D2: SS34; D_SMA
D3: CHG; LED_0805_2012Metric
H1, H2, H3, H4: MountingHole_3.2mm_M3
J1: YD-ESP32-S3_L; PinSocket_1x22_P2.54mm_Vertical
J2: YD-ESP32-S3_R; PinSocket_1x22_P2.54mm_Vertical
J3: ES8311_AUDIO; PinSocket_1x10_P2.54mm_Vertical
J4: TFT_1.77; PinHeader_1x07_P2.54mm_Vertical
J5: BAT_3V7; PinHeader_1x02_P2.54mm_Vertical
J6: SPARE_IO_A; PinHeader_1x08_P2.54mm_Vertical
J7: SPARE_IO_B; PinHeader_1x08_P2.54mm_Vertical
J8: PANEL_A; PinHeader_1x20_P2.54mm_Vertical
J9: UART1; PinHeader_1x03_P2.54mm_Vertical
J10: PANEL_B; PinHeader_1x20_P2.54mm_Vertical
L1: 22uH; L_Taiyo-Yuden_NR-60xx
R1: 1k; R_Axial_DIN0207_L6.3mm_D2.5mm_P7.62mm_Horizontal
R2: 2.4k; R_0805_2012Metric
R3: 1k; R_0805_2012Metric
R4: 71.5k; R_0805_2012Metric
R5: 10k; R_0805_2012Metric
R6, R7, R8, R9: 10k; R_0603_1608Metric
SW1: VOL_UP; SW_PUSH_6mm
SW2: VOL_DN; SW_PUSH_6mm
SW3: ACTIVATE; SW_PUSH_6mm
SW4: RESET; SW_PUSH_6mm
SW5: POWER_ON_OFF; SW_Slide_SPDT_Straight_CK_OS102011MS2Q
U1: TP4056; SOIC-8-1EP_3.9x4.9mm_P1.27mm_EP2.41x3.3mm_ThermalVias
U2: MT3608; SOT-23-6
U3, U4, U5, U6: 74HC595; SOIC-16_3.9x9.9mm_P1.27mm

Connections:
+3V3: C3.1, C4.1, C9.1, C10.1, C11.1, C12.1, J1.1, J1.2, J3.8, J4.6, J6.1, J7.1, J10.17, J10.18, J10.19, J10.20, R9.2, U3.10, U3.16, U4.10, U4.16, U5.10, U5.16, U6.10, U6.16
+5V: C1.1, C2.1, C5.1, C8.1, D2.1, J1.21, J3.9, R1.1, R3.1, R4.1, U1.4, U1.8
BTN_ACT: J1.12, SW3.1
BTN_RST: J1.3, SW4.1
BTN_VOL_DN: J1.5, SW2.1
BTN_VOL_UP: J1.4, SW1.1
CHG_A: D3.2, R3.2
CHRG: D3.1, U1.7
CSEL0: J10.8, U5.5
CSEL1: J10.9, U5.6
CSEL2: J10.10, U5.7
CSEL3: J8.15, U6.15
CSEL4: J8.14, U6.1
CSEL5: J10.11, U6.2
CSEL6: J10.12, U6.3
CSEL7: J10.13, U6.4
CSEL8: J10.14, U6.5
CSEL9: J10.15, U6.6
DRV_CASC1: U3.9, U4.14
DRV_CASC2: U4.9, U5.14
DRV_CASC3: U5.9, U6.14
FB: R4.2, R5.1, U2.3
GND: C1.2, C2.2, C3.2, C4.2, C5.2, C6.2, C7.2, C8.2, C9.2, C10.2, C11.2, C12.2, D1.1, J1.22, J2.1, J2.21, J2.22, J3.10, J4.7, J5.2, J6.2, J7.2, J8.16, J8.17, J8.18, J8.19, J9.3, J10.16, R2.2, R5.2, R6.2, R7.2, R8.2, SW1.2, SW2.2, SW3.2, SW4.2, U1.1, U1.3, U1.9, U2.2, U3.8, U4.8, U5.8, U6.8
I2C_SCL: J2.5, J3.2
I2C_SDA: J2.4, J3.1
I2S_BCK: J1.8, J3.4
I2S_DI: J1.7, J3.5
I2S_DO: J1.6, J3.7
I2S_MCK: J1.13, J3.3
I2S_WS: J1.9, J3.6
IO9: J1.15, J6.3, R6.1, U3.14
IO10: J1.16, J6.4, R7.1, U3.11, U4.11, U5.11, U6.11
IO11: J1.17, J6.5, R8.1, U3.12, U4.12, U5.12, U6.12
IO12: J1.18, J6.6, R9.1, U3.13, U4.13, U5.13, U6.13
IO13: J1.19, J6.7
IO14: J1.20, J6.8
IO17: J1.10, J9.1
IO18: J1.11, J9.2
IO38: J2.10, J7.5
IO39: J2.9, J7.4
IO42: J2.6, J7.3
IO43: J2.2, J7.7
IO44: J2.3, J7.8
IO48: J2.16, J7.6
LCD_CS: J2.7, J4.1
LCD_DC: J2.8, J4.2
LCD_RST: J2.15, J4.3
LCD_SCK: J2.18, J4.5
LCD_SDA: J2.17, J4.4
LED_A: D1.2, R1.2
PROG: R2.1, U1.2
ROW0: J8.2, U3.15
ROW1: J8.3, U3.1
ROW2: J8.4, U3.2
ROW3: J8.1, U3.3
ROW4: J8.5, U3.4
ROW5: J8.20, U3.5
ROW6: J8.6, U3.6
ROW7: J8.7, U3.7
ROW8: J8.8, U4.15
ROW9: J8.9, U4.1
ROW10: J10.1, U4.2
ROW11: J10.2, U4.3
ROW12: J10.3, U4.4
ROW13: J8.10, U4.5
ROW14: J8.11, U4.6
ROW15: J10.4, U4.7
ROW16: J8.12, U5.15
ROW17: J8.13, U5.1
ROW18: J10.5, U5.2
ROW19: J10.6, U5.3
ROW20: J10.7, U5.4
SW_NODE: D2.2, L1.2, U2.1
VBAT: C6.1, J5.1, SW5.2, U1.5
VBAT_SW: C7.1, L1.1, SW5.1, U2.4, U2.5

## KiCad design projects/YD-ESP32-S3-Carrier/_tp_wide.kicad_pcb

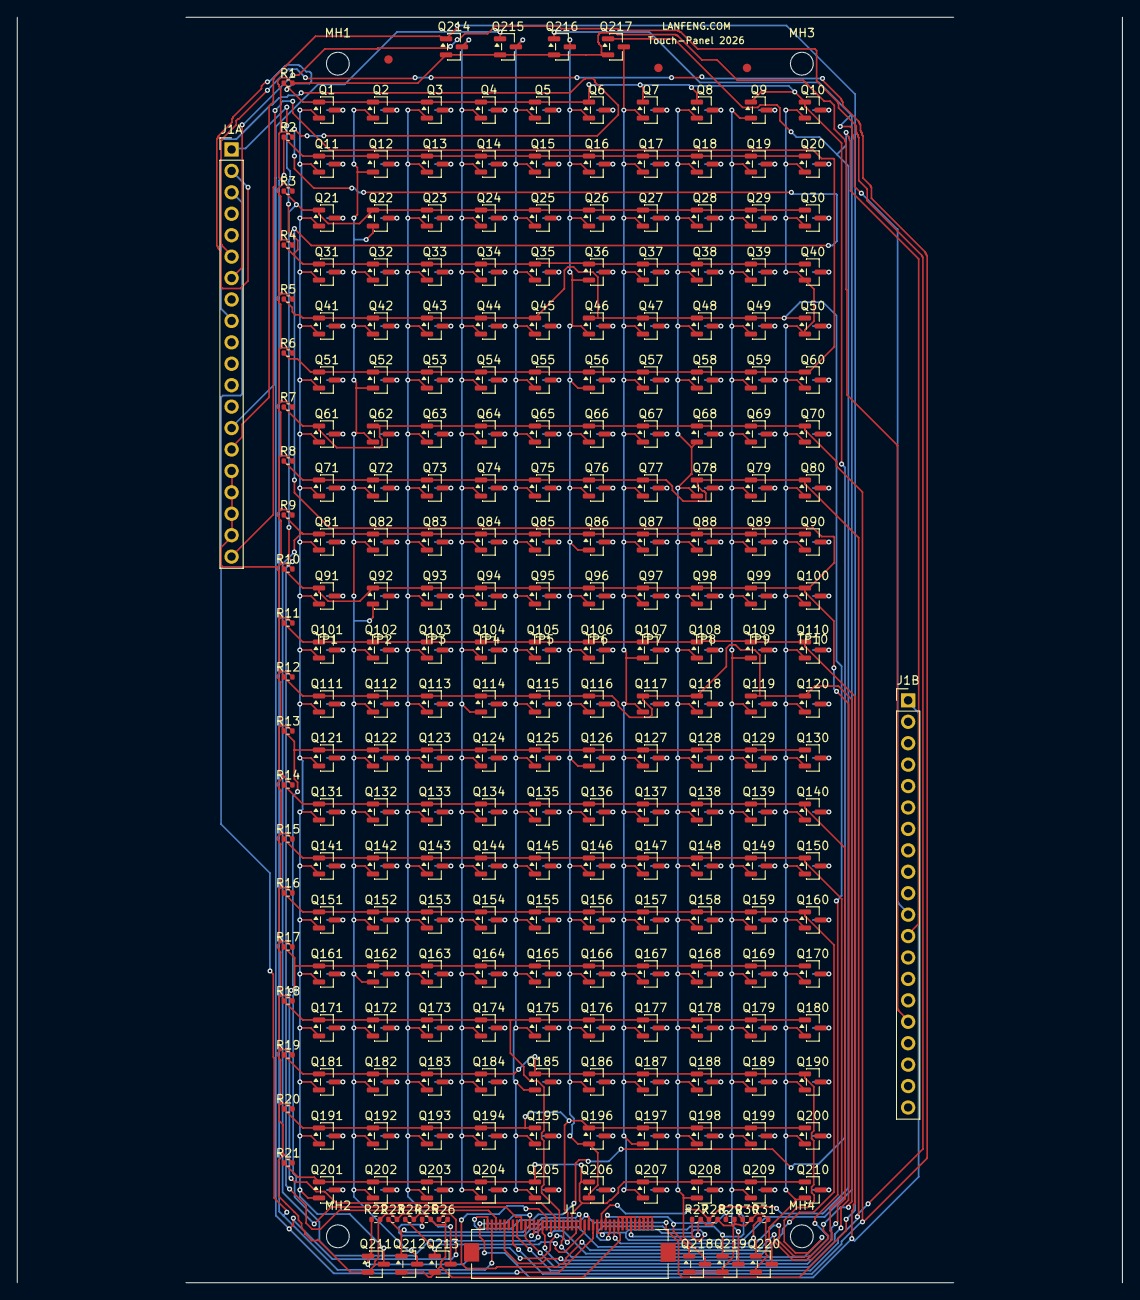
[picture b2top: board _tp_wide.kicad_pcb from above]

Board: 2 copper layers, 131.0 x 150.0 mm, 271 parts (0 on the bottom side), 253 nets.

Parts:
J1: FPC-40P-0.5mm; Hirose_FH12-40S-0.5SH_1x40-1MP_P0.50mm_Horizontal
J1A, J1B: PinHeader_1x20_P2.54mm_Vertical
MH1, MH2, MH3, MH4: MountingHole_2.7mm
MK1, MK2, MK3: Fiducial_1mm_Mask2mm
Q1, Q2, Q3, Q4, Q5, Q6, Q7, Q8, Q9, Q10, Q11, Q12, Q13, Q14, Q15, Q16, Q17, Q18, Q19, Q20, Q21, Q22, Q23, Q24, Q25, Q26, Q27, Q28, Q29, Q30, Q31, Q32, Q33, Q34, Q35, Q36, Q37, Q38, Q39, Q40, Q41, Q42, Q43, Q44, Q45, Q46, Q47, Q48, Q49, Q50, Q51, Q52, Q53, Q54, Q55, Q56, Q57, Q58, Q59, Q60, Q61, Q62, Q63, Q64, Q65, Q66, Q67, Q68, Q69, Q70, Q71, Q72, Q73, Q74, Q75, Q76, Q77, Q78, Q79, Q80, Q81, Q82, Q83, Q84, Q85, Q86, Q87, Q88, Q89, Q90, Q91, Q92, Q93, Q94, Q95, Q96, Q97, Q98, Q99, Q100, Q101, Q102, Q103, Q104, Q105, Q106, Q107, Q108, Q109, Q110, Q111, Q112, Q113, Q114, Q115, Q116, Q117, Q118, Q119, Q120, Q121, Q122, Q123, Q124, Q125, Q126, Q127, Q128, Q129, Q130, Q131, Q132, Q133, Q134, Q135, Q136, Q137, Q138, Q139, Q140, Q141, Q142, Q143, Q144, Q145, Q146, Q147, Q148, Q149, Q150, Q151, Q152, Q153, Q154, Q155, Q156, Q157, Q158, Q159, Q160, Q161, Q162, Q163, Q164, Q165, Q166, Q167, Q168, Q169, Q170, Q171, Q172, Q173, Q174, Q175, Q176, Q177, Q178, Q179, Q180, Q181, Q182, Q183, Q184, Q185, Q186, Q187, Q188, Q189, Q190, Q191, Q192, Q193, Q194, Q195, Q196, Q197, Q198, Q199, Q200, Q201, Q202, Q203, Q204, Q205, Q206, Q207, Q208, Q209, Q210, Q211, Q212, Q213, Q214, Q215, Q216, Q217, Q218, Q219, Q220: AO3400; SOT-23
R1, R2, R3, R4, R5, R6, R7, R8, R9, R10, R11, R12, R13, R14, R15, R16, R17, R18, R19, R20, R21, R22, R23, R24, R25, R26, R27, R28, R29, R30, R31: 10k; R_0402_1005Metric
TP1, TP2, TP3, TP4, TP5, TP6, TP7, TP8, TP9, TP10: TouchPadColumn

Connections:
+3V3: J1.37, J1.38, J1.39, J1.40
COL0: Q1.2, Q11.2, Q21.2, Q31.2, Q41.2, Q51.2, Q61.2, Q71.2, Q81.2, Q91.2, Q101.2, Q111.2, Q121.2, Q131.2, Q141.2, Q151.2, Q161.2, Q171.2, Q181.2, Q191.2, Q201.2, Q211.3
COL1: Q2.2, Q12.2, Q22.2, Q32.2, Q42.2, Q52.2, Q62.2, Q72.2, Q82.2, Q92.2, Q102.2, Q112.2, Q122.2, Q132.2, Q142.2, Q152.2, Q162.2, Q172.2, Q182.2, Q192.2, Q202.2, Q212.3
COL2: Q3.2, Q13.2, Q23.2, Q33.2, Q43.2, Q53.2, Q63.2, Q73.2, Q83.2, Q93.2, Q103.2, Q113.2, Q123.2, Q133.2, Q143.2, Q153.2, Q163.2, Q173.2, Q183.2, Q193.2, Q203.2, Q213.3
COL3: Q4.2, Q14.2, Q24.2, Q34.2, Q44.2, Q54.2, Q64.2, Q74.2, Q84.2, Q94.2, Q104.2, Q114.2, Q124.2, Q134.2, Q144.2, Q154.2, Q164.2, Q174.2, Q184.2, Q194.2, Q204.2, Q214.3
COL4: Q5.2, Q15.2, Q25.2, Q35.2, Q45.2, Q55.2, Q65.2, Q75.2, Q85.2, Q95.2, Q105.2, Q115.2, Q125.2, Q135.2, Q145.2, Q155.2, Q165.2, Q175.2, Q185.2, Q195.2, Q205.2, Q215.3
COL5: Q6.2, Q16.2, Q26.2, Q36.2, Q46.2, Q56.2, Q66.2, Q76.2, Q86.2, Q96.2, Q106.2, Q116.2, Q126.2, Q136.2, Q146.2, Q156.2, Q166.2, Q176.2, Q186.2, Q196.2, Q206.2, Q216.3
COL6: Q7.2, Q17.2, Q27.2, Q37.2, Q47.2, Q57.2, Q67.2, Q77.2, Q87.2, Q97.2, Q107.2, Q117.2, Q127.2, Q137.2, Q147.2, Q157.2, Q167.2, Q177.2, Q187.2, Q197.2, Q207.2, Q217.3
COL7: Q8.2, Q18.2, Q28.2, Q38.2, Q48.2, Q58.2, Q68.2, Q78.2, Q88.2, Q98.2, Q108.2, Q118.2, Q128.2, Q138.2, Q148.2, Q158.2, Q168.2, Q178.2, Q188.2, Q198.2, Q208.2, Q218.3
COL8: Q9.2, Q19.2, Q29.2, Q39.2, Q49.2, Q59.2, Q69.2, Q79.2, Q89.2, Q99.2, Q109.2, Q119.2, Q129.2, Q139.2, Q149.2, Q159.2, Q169.2, Q179.2, Q189.2, Q199.2, Q209.2, Q219.3
COL9: Q10.2, Q20.2, Q30.2, Q40.2, Q50.2, Q60.2, Q70.2, Q80.2, Q90.2, Q100.2, Q110.2, Q120.2, Q130.2, Q140.2, Q150.2, Q160.2, Q170.2, Q180.2, Q190.2, Q200.2, Q210.2, Q220.3
CSEL0: J1.22, Q211.1, R22.1
CSEL1: J1.23, Q212.1, R23.1
CSEL2: J1.24, Q213.1, R24.1
CSEL3: J1.25, J1A.15, Q214.1, R25.1
CSEL4: J1.26, J1A.14, Q215.1, R26.1
CSEL5: J1.27, J1B.11, Q216.1, R27.1
CSEL6: J1.28, J1B.12, Q217.1, R28.1
CSEL7: J1.29, Q218.1, R29.1
CSEL8: J1.30, Q219.1, R30.1
CSEL9: J1.31, Q220.1, R31.1
GND: J1.32, J1.33, J1.34, J1.35, J1.36, J1A.16, J1A.17, J1A.18, J1A.19, J1B.16, Q211.2, Q212.2, Q213.2, Q214.2, Q215.2, Q216.2, Q217.2, Q218.2, Q219.2, Q220.2, R1.2, R2.2, R3.2, R4.2, R5.2, R6.2, R7.2, R8.2, R9.2, R10.2, R11.2, R12.2, R13.2, R14.2, R15.2, R16.2, R17.2, R18.2, R19.2, R20.2, R21.2, R22.2, R23.2, R24.2, R25.2, R26.2, R27.2, R28.2, R29.2, R30.2, R31.2
PAD1: Q1.3, TP1.1
PAD2: Q2.3, TP2.1
PAD3: Q3.3, TP3.1
PAD4: Q4.3, TP4.1
PAD5: Q5.3, TP5.1
PAD6: Q6.3, TP6.1
PAD7: Q7.3, TP7.1
PAD8: Q8.3, TP8.1
PAD9: Q9.3, TP9.1
PAD10: Q10.3, TP10.1
PAD11: Q11.3, TP1.2
PAD12: Q12.3, TP2.2
PAD13: Q13.3, TP3.2
PAD14: Q14.3, TP4.2
PAD15: Q15.3, TP5.2
PAD16: Q16.3, TP6.2
PAD17: Q17.3, TP7.2
PAD18: Q18.3, TP8.2
PAD19: Q19.3, TP9.2
PAD20: Q20.3, TP10.2
PAD21: Q21.3, TP1.3
PAD22: Q22.3, TP2.3
PAD23: Q23.3, TP3.3
PAD24: Q24.3, TP4.3
PAD25: Q25.3, TP5.3
PAD26: Q26.3, TP6.3
PAD27: Q27.3, TP7.3
PAD28: Q28.3, TP8.3
PAD29: Q29.3, TP9.3
PAD30: Q30.3, TP10.3
PAD31: Q31.3, TP1.4
PAD32: Q32.3, TP2.4
PAD33: Q33.3, TP3.4
PAD34: Q34.3, TP4.4
PAD35: Q35.3, TP5.4
PAD36: Q36.3, TP6.4
PAD37: Q37.3, TP7.4
PAD38: Q38.3, TP8.4
PAD39: Q39.3, TP9.4
PAD40: Q40.3, TP10.4
PAD41: Q41.3, TP1.5
PAD42: Q42.3, TP2.5
PAD43: Q43.3, TP3.5
PAD44: Q44.3, TP4.5
PAD45: Q45.3, TP5.5
PAD46: Q46.3, TP6.5
PAD47: Q47.3, TP7.5
PAD48: Q48.3, TP8.5
PAD49: Q49.3, TP9.5
PAD50: Q50.3, TP10.5
PAD51: Q51.3, TP1.6
PAD52: Q52.3, TP2.6
PAD53: Q53.3, TP3.6
PAD54: Q54.3, TP4.6
PAD55: Q55.3, TP5.6
PAD56: Q56.3, TP6.6
PAD57: Q57.3, TP7.6
PAD58: Q58.3, TP8.6
PAD59: Q59.3, TP9.6
PAD60: Q60.3, TP10.6
PAD61: Q61.3, TP1.7
PAD62: Q62.3, TP2.7
PAD63: Q63.3, TP3.7
PAD64: Q64.3, TP4.7
PAD65: Q65.3, TP5.7
PAD66: Q66.3, TP6.7
PAD67: Q67.3, TP7.7
PAD68: Q68.3, TP8.7
PAD69: Q69.3, TP9.7
PAD70: Q70.3, TP10.7
PAD71: Q71.3, TP1.8
PAD72: Q72.3, TP2.8
PAD73: Q73.3, TP3.8
PAD74: Q74.3, TP4.8
PAD75: Q75.3, TP5.8
PAD76: Q76.3, TP6.8
PAD77: Q77.3, TP7.8
PAD78: Q78.3, TP8.8
PAD79: Q79.3, TP9.8
PAD80: Q80.3, TP10.8
PAD81: Q81.3, TP1.9
PAD82: Q82.3, TP2.9
PAD83: Q83.3, TP3.9
PAD84: Q84.3, TP4.9
PAD85: Q85.3, TP5.9
PAD86: Q86.3, TP6.9
PAD87: Q87.3, TP7.9
PAD88: Q88.3, TP8.9
PAD89: Q89.3, TP9.9
PAD90: Q90.3, TP10.9
PAD91: Q91.3, TP1.10
PAD92: Q92.3, TP2.10
PAD93: Q93.3, TP3.10
PAD94: Q94.3, TP4.10
PAD95: Q95.3, TP5.10
PAD96: Q96.3, TP6.10
PAD97: Q97.3, TP7.10
PAD98: Q98.3, TP8.10
PAD99: Q99.3, TP9.10
PAD100: Q100.3, TP10.10
PAD101: Q101.3, TP1.11
PAD102: Q102.3, TP2.11
PAD103: Q103.3, TP3.11
PAD104: Q104.3, TP4.11
PAD105: Q105.3, TP5.11
PAD106: Q106.3, TP6.11
PAD107: Q107.3, TP7.11
PAD108: Q108.3, TP8.11
PAD109: Q109.3, TP9.11
PAD110: Q110.3, TP10.11
PAD111: Q111.3, TP1.12
PAD112: Q112.3, TP2.12
PAD113: Q113.3, TP3.12
PAD114: Q114.3, TP4.12
PAD115: Q115.3, TP5.12
PAD116: Q116.3, TP6.12
PAD117: Q117.3, TP7.12
PAD118: Q118.3, TP8.12
PAD119: Q119.3, TP9.12
PAD120: Q120.3, TP10.12
PAD121: Q121.3, TP1.13
PAD122: Q122.3, TP2.13
PAD123: Q123.3, TP3.13
PAD124: Q124.3, TP4.13
PAD125: Q125.3, TP5.13
PAD126: Q126.3, TP6.13
PAD127: Q127.3, TP7.13
PAD128: Q128.3, TP8.13
PAD129: Q129.3, TP9.13
PAD130: Q130.3, TP10.13
PAD131: Q131.3, TP1.14
PAD132: Q132.3, TP2.14
PAD133: Q133.3, TP3.14
PAD134: Q134.3, TP4.14
PAD135: Q135.3, TP5.14
PAD136: Q136.3, TP6.14
PAD137: Q137.3, TP7.14
PAD138: Q138.3, TP8.14
PAD139: Q139.3, TP9.14
PAD140: Q140.3, TP10.14
PAD141: Q141.3, TP1.15
PAD142: Q142.3, TP2.15
PAD143: Q143.3, TP3.15
PAD144: Q144.3, TP4.15
PAD145: Q145.3, TP5.15
PAD146: Q146.3, TP6.15
PAD147: Q147.3, TP7.15
PAD148: Q148.3, TP8.15
PAD149: Q149.3, TP9.15
PAD150: Q150.3, TP10.15
PAD151: Q151.3, TP1.16
PAD152: Q152.3, TP2.16
PAD153: Q153.3, TP3.16
PAD154: Q154.3, TP4.16
PAD155: Q155.3, TP5.16
PAD156: Q156.3, TP6.16
PAD157: Q157.3, TP7.16
PAD158: Q158.3, TP8.16
PAD159: Q159.3, TP9.16
PAD160: Q160.3, TP10.16
PAD161: Q161.3, TP1.17
PAD162: Q162.3, TP2.17
PAD163: Q163.3, TP3.17
PAD164: Q164.3, TP4.17
PAD165: Q165.3, TP5.17
PAD166: Q166.3, TP6.17
PAD167: Q167.3, TP7.17
PAD168: Q168.3, TP8.17
PAD169: Q169.3, TP9.17
PAD170: Q170.3, TP10.17
PAD171: Q171.3, TP1.18
PAD172: Q172.3, TP2.18
PAD173: Q173.3, TP3.18
PAD174: Q174.3, TP4.18
PAD175: Q175.3, TP5.18
PAD176: Q176.3, TP6.18
PAD177: Q177.3, TP7.18
PAD178: Q178.3, TP8.18
PAD179: Q179.3, TP9.18
PAD180: Q180.3, TP10.18
PAD181: Q181.3, TP1.19
PAD182: Q182.3, TP2.19
PAD183: Q183.3, TP3.19
PAD184: Q184.3, TP4.19
PAD185: Q185.3, TP5.19
PAD186: Q186.3, TP6.19
PAD187: Q187.3, TP7.19
PAD188: Q188.3, TP8.19
PAD189: Q189.3, TP9.19
PAD190: Q190.3, TP10.19
PAD191: Q191.3, TP1.20
PAD192: Q192.3, TP2.20
PAD193: Q193.3, TP3.20
PAD194: Q194.3, TP4.20
PAD195: Q195.3, TP5.20
PAD196: Q196.3, TP6.20
PAD197: Q197.3, TP7.20
PAD198: Q198.3, TP8.20
PAD199: Q199.3, TP9.20
PAD200: Q200.3, TP10.20
PAD201: Q201.3, TP1.21
PAD202: Q202.3, TP2.21
PAD203: Q203.3, TP3.21
PAD204: Q204.3, TP4.21
PAD205: Q205.3, TP5.21
PAD206: Q206.3, TP6.21
PAD207: Q207.3, TP7.21
PAD208: Q208.3, TP8.21
PAD209: Q209.3, TP9.21
PAD210: Q210.3, TP10.21
ROW0: J1.1, J1A.2, Q1.1, Q2.1, Q3.1, Q4.1, Q5.1, Q6.1, Q7.1, Q8.1, Q9.1, Q10.1, R1.1
ROW1: J1.2, J1A.3, Q11.1, Q12.1, Q13.1, Q14.1, Q15.1, Q16.1, Q17.1, Q18.1, Q19.1, Q20.1, R2.1
ROW2: J1.3, Q21.1, Q22.1, Q23.1, Q24.1, Q25.1, Q26.1, Q27.1, Q28.1, Q29.1, Q30.1, R3.1
ROW3: J1.4, J1A.1, Q31.1, Q32.1, Q33.1, Q34.1, Q35.1, Q36.1, Q37.1, Q38.1, Q39.1, Q40.1, R4.1
ROW4: J1.5, Q41.1, Q42.1, Q43.1, Q44.1, Q45.1, Q46.1, Q47.1, Q48.1, Q49.1, Q50.1, R5.1
ROW5: J1.6, J1A.20, Q51.1, Q52.1, Q53.1, Q54.1, Q55.1, Q56.1, Q57.1, Q58.1, Q59.1, Q60.1, R6.1
ROW6: J1.7, J1A.6, Q61.1, Q62.1, Q63.1, Q64.1, Q65.1, Q66.1, Q67.1, Q68.1, Q69.1, Q70.1, R7.1
ROW7: J1.8, J1A.7, Q71.1, Q72.1, Q73.1, Q74.1, Q75.1, Q76.1, Q77.1, Q78.1, Q79.1, Q80.1, R8.1
ROW8: J1.9, Q81.1, Q82.1, Q83.1, Q84.1, Q85.1, Q86.1, Q87.1, Q88.1, Q89.1, Q90.1, R9.1
ROW9: J1.10, J1A.9, Q91.1, Q92.1, Q93.1, Q94.1, Q95.1, Q96.1, Q97.1, Q98.1, Q99.1, Q100.1, R10.1
ROW10: J1.11, J1B.1, Q101.1, Q102.1, Q103.1, Q104.1, Q105.1, Q106.1, Q107.1, Q108.1, Q109.1, Q110.1, R11.1
ROW11: J1.12, Q111.1, Q112.1, Q113.1, Q114.1, Q115.1, Q116.1, Q117.1, Q118.1, Q119.1, Q120.1, R12.1
ROW12: J1.13, Q121.1, Q122.1, Q123.1, Q124.1, Q125.1, Q126.1, Q127.1, Q128.1, Q129.1, Q130.1, R13.1
ROW13: J1.14, Q131.1, Q132.1, Q133.1, Q134.1, Q135.1, Q136.1, Q137.1, Q138.1, Q139.1, Q140.1, R14.1
ROW14: J1.15, Q141.1, Q142.1, Q143.1, Q144.1, Q145.1, Q146.1, Q147.1, Q148.1, Q149.1, Q150.1, R15.1
ROW15: J1.16, Q151.1, Q152.1, Q153.1, Q154.1, Q155.1, Q156.1, Q157.1, Q158.1, Q159.1, Q160.1, R16.1
ROW16: J1.17, Q161.1, Q162.1, Q163.1, Q164.1, Q165.1, Q166.1, Q167.1, Q168.1, Q169.1, Q170.1, R17.1
ROW17: J1.18, Q171.1, Q172.1, Q173.1, Q174.1, Q175.1, Q176.1, Q177.1, Q178.1, Q179.1, Q180.1, R18.1
ROW18: J1.19, Q181.1, Q182.1, Q183.1, Q184.1, Q185.1, Q186.1, Q187.1, Q188.1, Q189.1, Q190.1, R19.1
ROW19: J1.20, Q191.1, Q192.1, Q193.1, Q194.1, Q195.1, Q196.1, Q197.1, Q198.1, Q199.1, Q200.1, R20.1
ROW20: J1.21, Q201.1, Q202.1, Q203.1, Q204.1, Q205.1, Q206.1, Q207.1, Q208.1, Q209.1, Q210.1, R21.1

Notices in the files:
README.md:
License:
This project is licensed under the MIT License. See [LICENSE](LICENSE) for details.
Citation:
If you use this project in your research or publication, please cite:
@software{kicad_mcp_server,
title = {KiCAD MCP Server: AI-Assisted PCB Design},
author = {mixelpixx},
year = {2025},
url = {https://github.com/mixelpixx/KiCAD-MCP-Server},
version = {2.3.0}
